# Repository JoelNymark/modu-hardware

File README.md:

# modu-hardware

KiCad hardware design files, schematics, PCB layouts, and 3D models for the **Modu** modular macro pad system. Modules connect magnetically via 4-pin pogo headers and communicate over a shared CAN bus.

> [!NOTE]
<!-- > Companion desktop control software: **[modu-app](https://github.com/RealWinter/modu-app)** -->

---

## Hardware Modules

| Hub Module (`hub-pcb`) | 4x4 Keypad Module (`4x4-key-pcb`) |
| :---: | :---: |
|  |  |
| Primary USB-C host controller and power/CAN bus bridge. | Snap-on 16-key mechanical switch matrix module. |

### 1. Hub PCB (`hub-pcb`)
The master controller module that interfaces with the host PC over USB-C and distributes power and CAN bus communication to connected satellite modules.
* **MCU:** STM32G0B1CBT6 (`U2`)
* **CAN Transceiver:** SN65HVD230DR (`U3`)
* **Power & Protection:** 3.3V regulation (`U1`), USB-C ESD protection (`U4`), and input reverse/surge protection (`D1`, `D2`)
* **Interconnects:** 6x perimeter 4-pin pogo pin header footprints (left, right, and bottom edges) for multi-directional module docking, plus SWD/debug headers (`J8`)

### 2. 4x4 Keypad PCB (`4x4-key-pcb`)
A 16-key modular keypad expansion board that can dock to the Hub or daisy-chain to other modules from any side.
* **MCU:** STM32G071CBT6 (`U2`)
* **CAN Transceiver:** SN65HVD230DR (`U3`)
* **Switch Matrix:** 4x4 mechanical key switch layout with individual per-key 1N4148W anti-ghosting diodes (`D1`–`D16`)
* **Interconnects:** 16x perimeter 4-pin pogo pin headers (4 per edge across all 4 sides) allowing flexible orientation and chaining

---

## Repository Structure

```text
modu-hardware/
├── hub-pcb/          # KiCad project, schematic, PCB, and STEP model for the Hub module
├── 4x4-key-pcb/      # KiCad project, schematic, PCB, and STEP model for the 4x4 Keypad module
├── hub-pcb.png       # 3D render of the Hub PCB
└── 4x4-key-pcb.png   # 3D render of the 4x4 Keypad PCB

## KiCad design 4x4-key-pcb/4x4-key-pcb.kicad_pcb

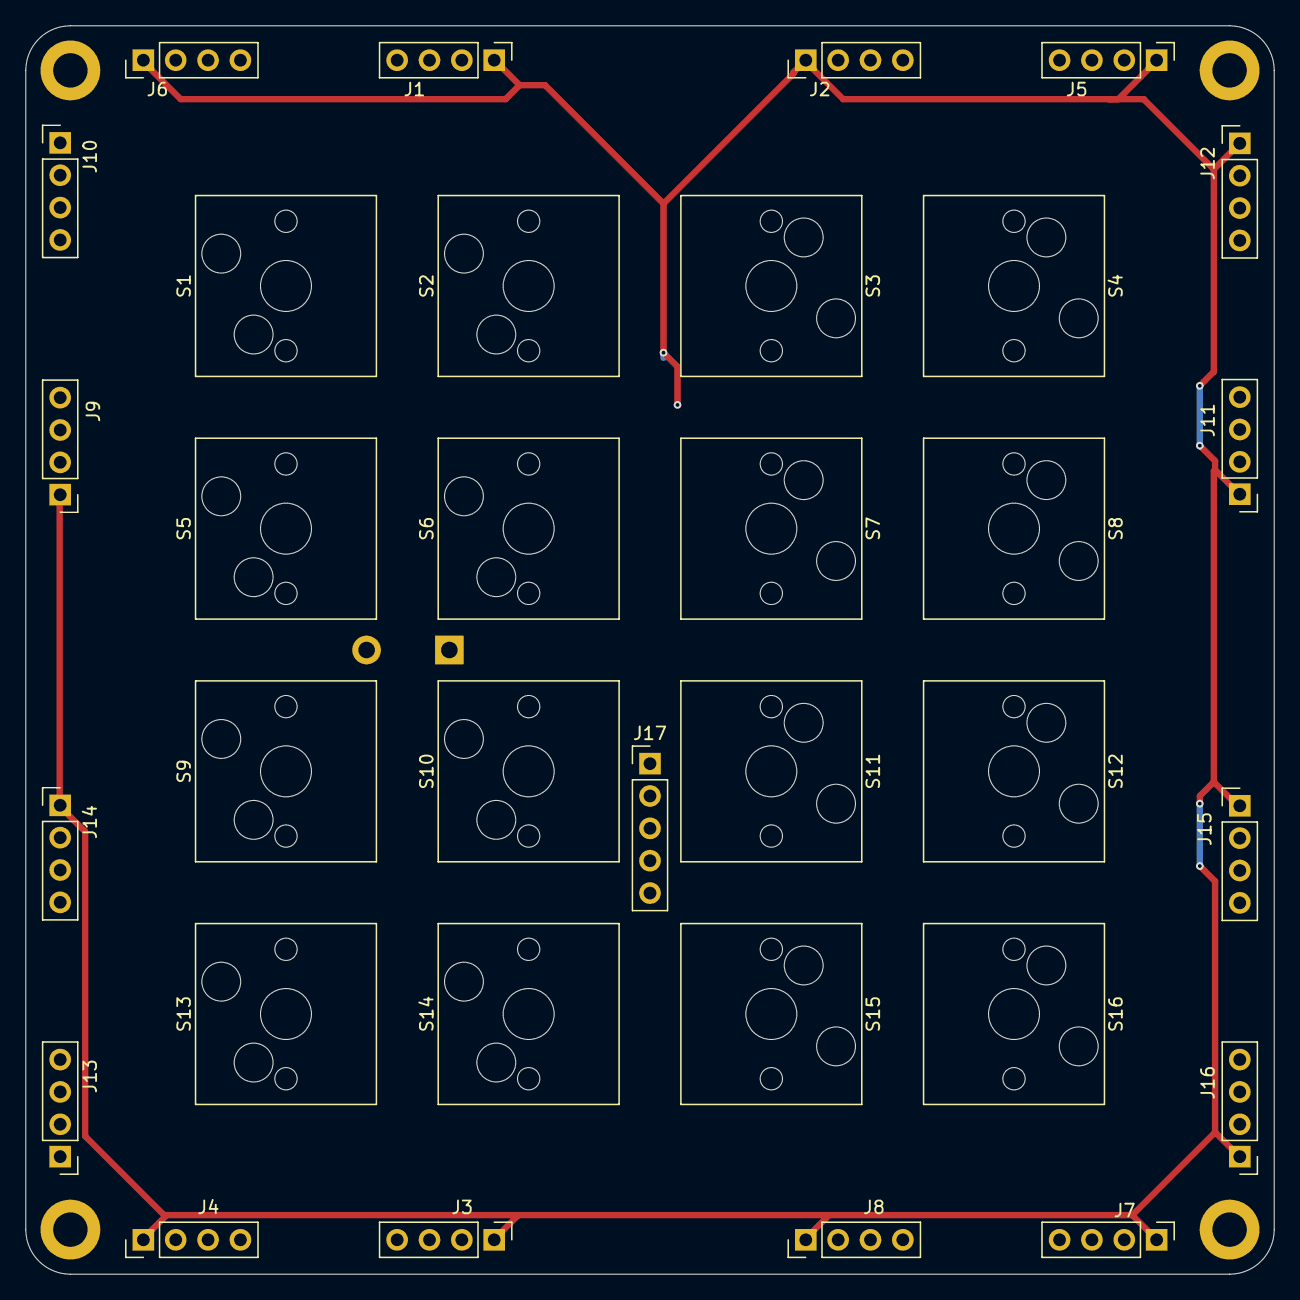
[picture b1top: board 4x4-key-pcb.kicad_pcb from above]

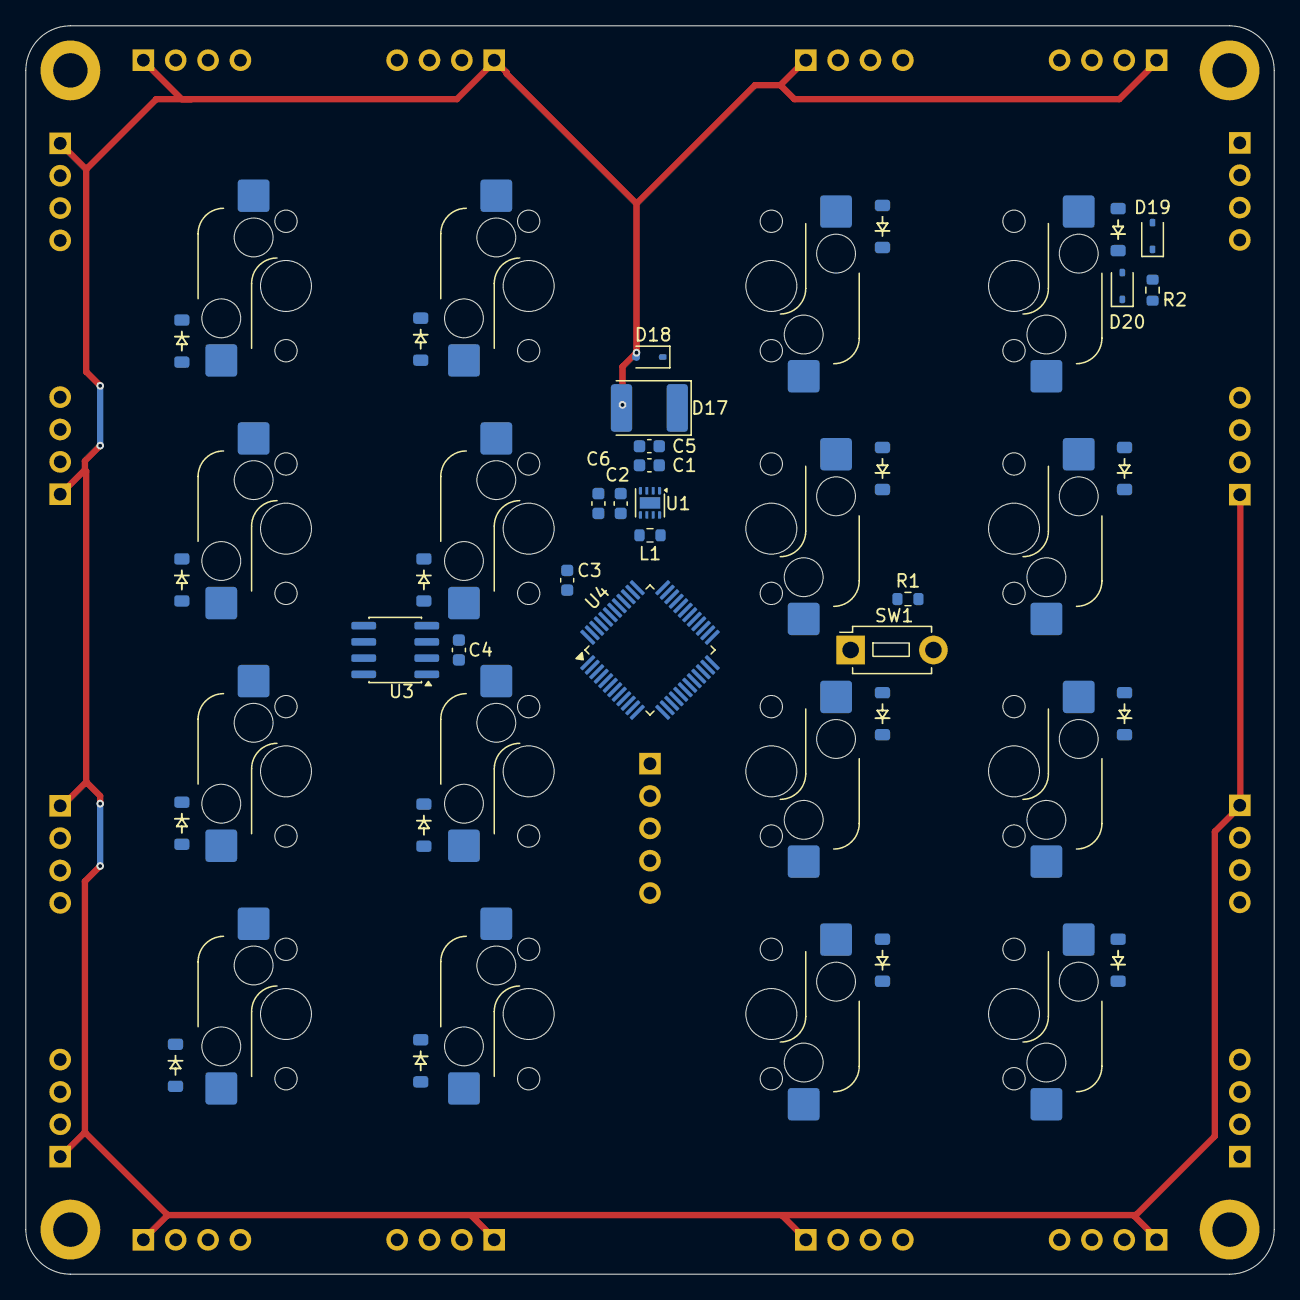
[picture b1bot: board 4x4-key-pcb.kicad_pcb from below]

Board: 2 copper layers, 98.0 x 98.0 mm, 66 parts (33 on the bottom side), 36 nets.

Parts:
C1: 10uF; C_0603_1608Metric
C2: 22uF; C_0603_1608Metric
C3, C4, C5, C6: 100nF; C_0603_1608Metric
D1, D2, D3, D4, D5, D6, D7, D8, D9, D10, D11, D12, D13, D14, D15, D16: Diode_SOD-123
D17: D_Schottky; D_2114_3652Metric
D18: 5.6V; D_SOD-323
D19, D20: D_TVS; D_SOD-323
J1, J2, J3, J4, J5, J6, J7, J8, J9, J10, J11, J12, J13, J14, J15, J16: Conn_01x04_Socket; PinHeader_1x04_P2.54mm_Vertical
J17: Conn_01x05_Pin; PinHeader_1x05_P2.54mm_Vertical
L1: 2.2uH; R_0603_1608Metric
R1: 10kΩ; R_0603_1608Metric
R2: R120Ω; R_0603_1608Metric
S1, S2, S3, S4, S5, S6, S7, S8, S9, S10, S11, S12, S13, S14, S15, S16: Hotswap_MX_1.00u
SW1: SW_Push; SW_PUSH_1P1T_6x3.5mm_H4.3_APEM_MJTP1243
U1: TPS62162DSG; Texas_DSG0008A_WSON-8-1EP_2x2mm_P0.5mm_EP0.9x1.6mm
U3: SN65HVD230; SOIC-8_3.9x4.9mm_P1.27mm
U4: STM32G0B1CBT6; LQFP-48_7x7mm_P0.5mm

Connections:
+3.3V: C2.1, C3.1, C4.1, C6.1, J17.1, L1.2, R1.1, U1.6 (VOS), U3.3 (VCC), U4.6 (VDD)
+5V: D17.2 (A), D18.2 (A2), J1.1, J2.1, J3.1, J4.1, J5.1, J6.1, J7.1, J8.1, J9.1, J10.1, J11.1, J12.1, J13.1, J14.1, J15.1, J16.1
C0: D1.1 (K), D2.1 (K), D3.1 (K), D4.1 (K), U4.21 (PB2)
C1: D5.1 (K), D6.1 (K), D7.1 (K), D8.1 (K), U4.42 (PB3)
C2: D9.1 (K), D10.1 (K), D11.1 (K), D12.1 (K), U4.45 (PB6)
C3: D13.1 (K), D14.1 (K), D15.1 (K), D16.1 (K), U4.46 (PB7)
CAN_H: D19.1 (A1), J1.3, J2.3, J3.3, J4.3, J5.3, J6.3, J7.3, J8.3, J9.3, J10.3, J11.3, J12.3, J13.3, J14.3, J15.3, J16.3, R2.1, U3.7 (CANH)
CAN_L: D20.1 (A1), J1.4, J2.4, J3.4, J4.4, J5.4, J6.4, J7.4, J8.4, J9.4, J10.4, J11.4, J12.4, J13.4, J14.4, J15.4, J16.4, R2.2, U3.6 (CANL)
CAN_RX: U3.4 (R), U4.33 (PA9/PA11)
CAN_TX: U3.1 (D), U4.32 (PA10/UCPD1_DBCC2)
GND: C1.2, C2.2, C3.2, C4.2, C5.1, C6.2, D18.1 (A1), D19.2 (A2), D20.2 (A2), J1.2, J2.2, J3.2, J4.2, J5.2, J6.2, J7.2, J8.2, J9.2, J10.2, J11.2, J12.2, J13.2, J14.2, J15.2, J16.2, J17.3, SW1.1, U1.1 (PGND), U1.4 (AGND), U1.5 (FB), U1.9 (PAD), U3.2 (GND), U3.8 (Rs), U4.7 (VSS)
unnamed: D1.2 (A), S1.2
unnamed: D2.2 (A), S2.2
unnamed: D3.2 (A), S3.2
unnamed: D4.2 (A), S4.2
unnamed: D5.2 (A), S5.2
unnamed: D6.2 (A), S6.2
unnamed: D7.2 (A), S7.2
unnamed: D8.2 (A), S8.2
unnamed: D9.2 (A), S9.2
unnamed: D10.2 (A), S10.2
unnamed: D11.2 (A), S11.2
unnamed: D12.2 (A), S12.2
unnamed: D13.2 (A), S13.2
unnamed: D14.2 (A), S14.2
unnamed: D15.2 (A), S15.2
unnamed: D16.2 (A), S16.2
unnamed: C1.1, C5.2, D17.1 (K), U1.2 (VIN), U1.3 (EN)
unnamed: L1.1, U1.7 (SW)
PF2: J17.5, R1.2, SW1.2, U4.10 (PF2)
R0: S1.1, S5.1, S9.1, S13.1, U4.19 (PB0)
R1: S2.1, S6.1, S10.1, S14.1, U4.20 (PB1)
R2: S3.1, S7.1, S11.1, S15.1, U4.43 (PB4)
R3: S4.1, S8.1, S12.1, S16.1, U4.44 (PB5)
SWCLK: J17.4, U4.36 (PA14)
SWDIO: J17.2, U4.35 (PA13)

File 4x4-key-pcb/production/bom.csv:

Designator,Footprint,Quantity,Value,LCSC Part #
C1,0603,1,10uF,
C2,0603,1,22uF,
"C3_2, C3, C4, C5, C6",0603,5,100nF,
"D1, D10, D11, D12, D13, D14, D15, D16, D2, D3, D4, D5, D6, D7, D8, D9",Diode_SOD-123,16,~,
D17,2114,1,D_Schottky,
"D18, D19, D20",D_SOD-323,3,D_TVS,
"J1, J10, J11, J12, J13, J14, J15, J16, J2, J3, J4, J5, J6, J7, J8, J9",PinHeader_1x04_P2.54mm_Vertical,16,Conn_01x04_Socket,
J17,PinHeader_1x05_P2.54mm_Vertical,1,Conn_01x05_Pin,
L1,0603,1,2.2uH,
R1,0603,1,10kΩ,
R2,0603,1,R120Ω,
"S1, S10, S11, S12, S13, S14, S15, S16, S2, S3, S4, S5, S6, S7, S8, S9",MX_PCB_1.00u,16,~,
SW1,SW_PUSH_1P1T_6x3.5mm_H4.3_APEM_MJTP1243,1,SW_Push,
U1,Texas_DSG0008A_WSON-8-1EP_2x2mm_P0.5mm_EP0.9x1.6mm,1,TPS62162DSG,
U3,SOIC-8_3.9x4.9mm_P1.27mm,1,SN65HVD230,
U4,LQFP-48_7x7mm_P0.5mm,1,STM32G0B1CBT6,

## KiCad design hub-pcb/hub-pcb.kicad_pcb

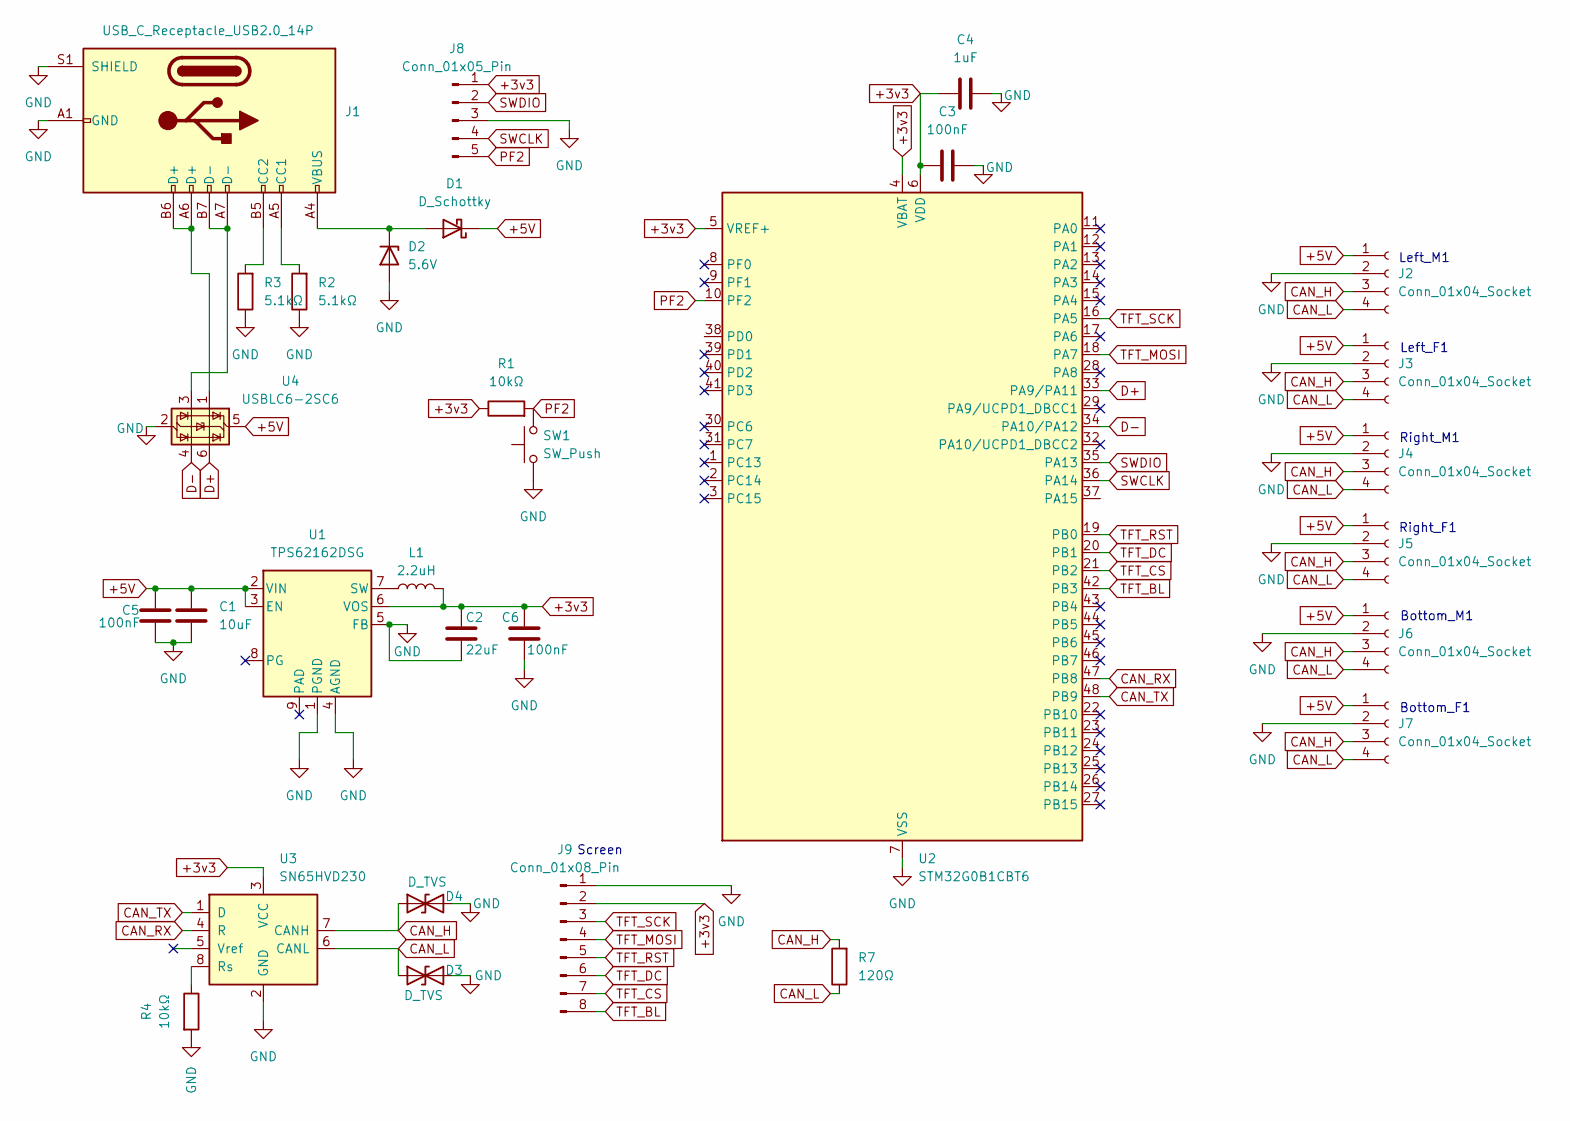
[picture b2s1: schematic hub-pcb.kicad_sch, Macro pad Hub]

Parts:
C1: 10uF; C_0603_1608Metric
C2: 22uF; C_0603_1608Metric
C3, C5, C6: 100nF; C_0603_1608Metric
C4: 1uF; C_0603_1608Metric
D1: D_Schottky; D_2114_3652Metric
D2: 5.6V; D_SOD-323
D3, D4: D_TVS; D_SOD-123
J1: USB_C_Receptacle_USB2.0_14P; USB_C_HRO_TYPE-C-31-M-12
J2, J3, J4, J5, J6, J7: Conn_01x04_Socket; PinHeader_1x04_P2.54mm_Vertical
J8: Conn_01x05_Pin; PinHeader_1x05_P2.54mm_Vertical
J9: Conn_01x08_Pin; PinHeader_1x08_P2.54mm_Vertical
L1: 2.2uH; R_0603_1608Metric
R1, R4: 10kΩ; R_0603_1608Metric
R2, R3: 5.1kΩ; R_0603_1608Metric
R7: 120Ω; R_0603_1608Metric
SW1: SW_Push; SW_PUSH_1P1T_6x3.5mm_H4.3_APEM_MJTP1243
U1: TPS62162DSG; Texas_DSG0008A_WSON-8-1EP_2x2mm_P0.5mm_EP0.9x1.6mm_ThermalV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
U2: STM32G0B1CBT6; LQFP-48_7x7mm_P0.5mm
U3: SN65HVD230; SOIC-8_3.9x4.9mm_P1.27mm
U4: USBLC6-2SC6; SOT-23-6

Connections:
+3v3: C2.1, C3.1, C4.1, C6.1, J8.1, J9.2, L1.2, R1.1, U1.6 (VOS), U2.4 (VBAT), U2.5 (VREF+), U2.6 (VDD), U3.3 (VCC)
+5V: C1.1, C5.1, D1.1 (K), J2.1, J3.1, J4.1, J5.1, J6.1, J7.1, U1.2 (VIN), U1.3 (EN), U4.5 (VBUS)
CAN_H: D4.1 (A1), J2.3, J3.3, J4.3, J5.3, J6.3, J7.3, R7.2, U3.7 (CANH)
CAN_L: D3.1 (A1), J2.4, J3.4, J4.4, J5.4, J6.4, J7.4, R7.1, U3.6 (CANL)
CAN_RX: U2.47 (PB8), U3.4 (R)
CAN_TX: U2.48 (PB9), U3.1 (D)
D+: U2.33 (PA9/PA11), U4.6 (I/O1)
D-: U2.34 (PA10/PA12), U4.4 (I/O2)
GND: C1.2, C2.2, C3.2, C4.2, C5.2, C6.2, D2.2 (A), D3.2 (A2), D4.2 (A2), J1.A1 (GND), J1.A12 (GND), J1.B1 (GND), J1.B12 (GND), J1.S1 (SHIELD), J2.2, J3.2, J4.2, J5.2, J6.2, J7.2, J8.3, J9.1, R2.1, R3.1, R4.2, SW1.1, U1.1 (PGND), U1.4 (AGND), U1.5 (FB), U2.7 (VSS), U3.2 (GND), U4.2 (GND)
unnamed: D1.2 (A), D2.1 (K), J1.A4 (VBUS), J1.A9 (VBUS), J1.B4 (VBUS), J1.B9 (VBUS)
unnamed: J1.A5 (CC1), R2.2
unnamed: J1.B5 (CC2), R3.2
unnamed: J1.A6 (D+), J1.B6 (D+), U4.1 (I/O1)
unnamed: J1.A7 (D-), J1.B7 (D-), U4.3 (I/O2)
unnamed: L1.1, U1.7 (SW)
unnamed: R4.1, U3.8 (Rs)
PF2: J8.5, R1.2, SW1.2, U2.10 (PF2)
SWCLK: J8.4, U2.36 (PA14)
SWDIO: J8.2, U2.35 (PA13)
TFT_BL: J9.8, U2.42 (PB3)
TFT_CS: J9.7, U2.21 (PB2)
TFT_DC: J9.6, U2.20 (PB1)
TFT_MOSI: J9.4, U2.18 (PA7)
TFT_RST: J9.5, U2.19 (PB0)
TFT_SCK: J9.3, U2.16 (PA5)

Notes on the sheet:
Right_M1
Right_F1
Left_M1
Left_F1
Bottom_F1
Screen
Bottom_M1

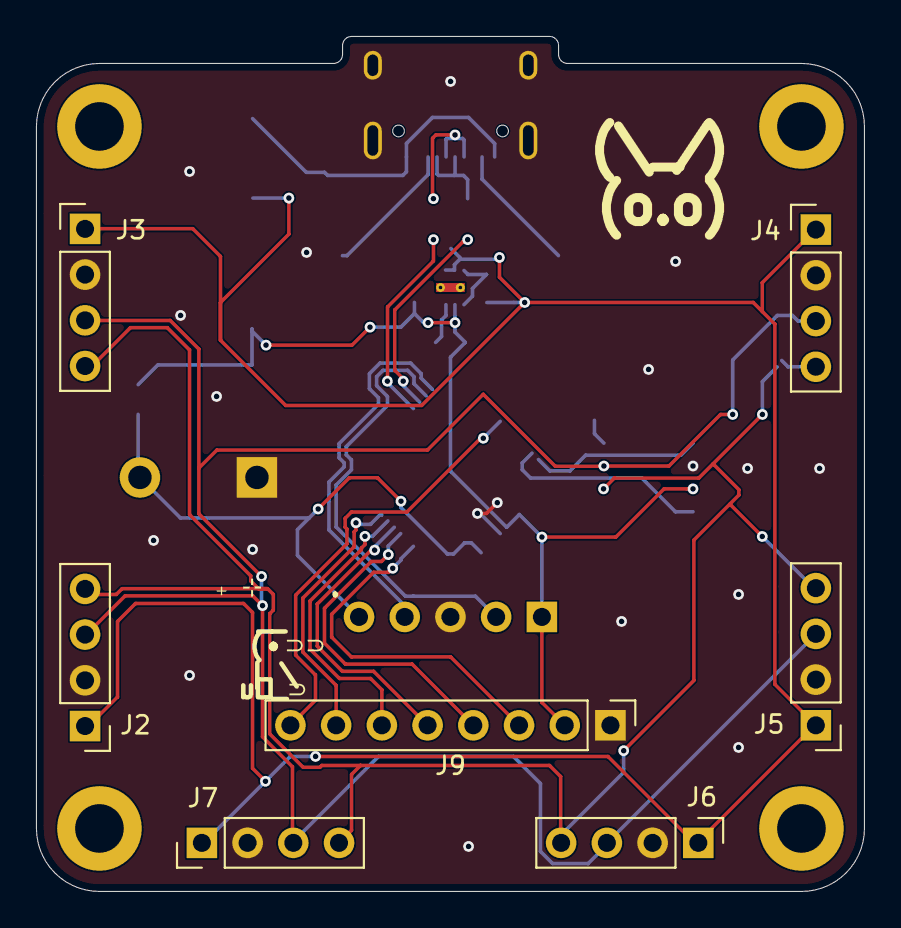
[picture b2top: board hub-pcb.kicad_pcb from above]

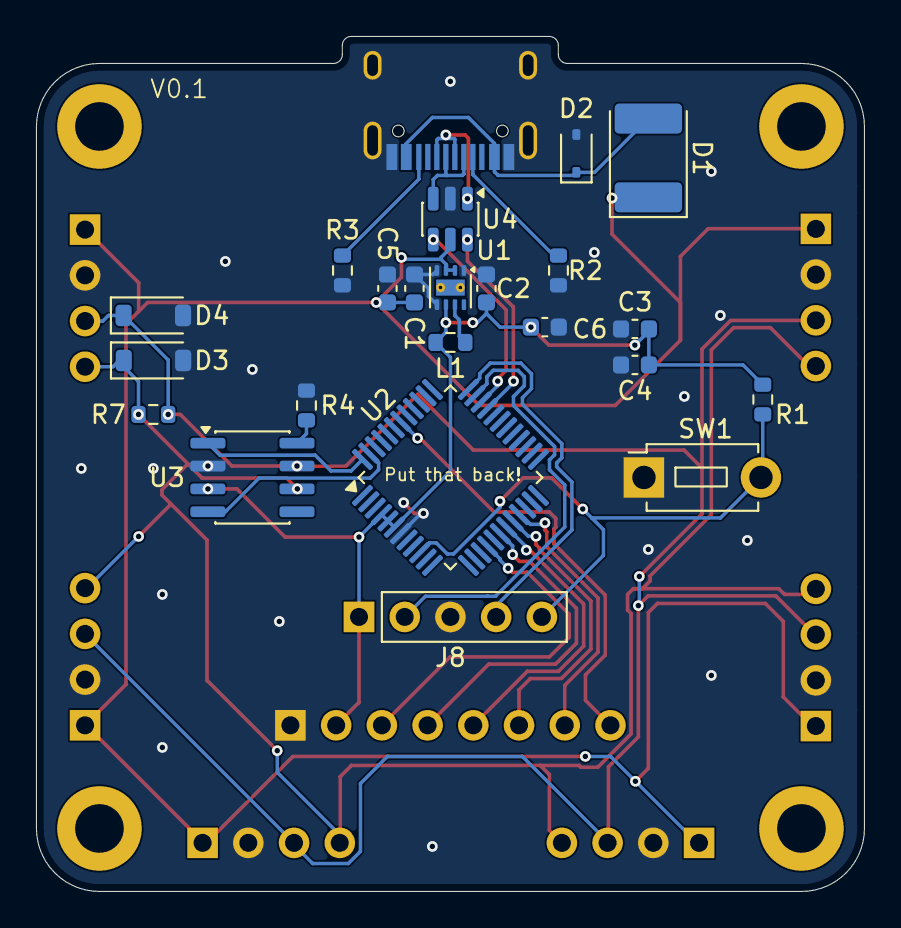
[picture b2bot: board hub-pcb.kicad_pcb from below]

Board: 2 copper layers, 46.0 x 47.5 mm, 30 parts (23 on the bottom side), 25 nets.

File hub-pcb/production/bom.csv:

Designator,Footprint,Quantity,Value,LCSC Part #
C1,0603,1,10uF,
C2,0603,1,22uF,
"C3, C5, C6",0603,3,100nF,
C4,0603,1,1uF,
D1,2114,1,D_Schottky,
D2,D_SOD-323,1,5.6V,
"D3, D4",D_SOD-123,2,D_TVS,
J1,USB_C_HRO_TYPE-C-31-M-12,1,USB_C_Receptacle_USB2.0_14P,
"J2, J3, J4, J5, J6, J7",PinHeader_1x04_P2.54mm_Vertical,6,Conn_01x04_Socket,
J8,PinHeader_1x05_P2.54mm_Vertical,1,Conn_01x05_Pin,
J9,PinHeader_1x08_P2.54mm_Vertical,1,Conn_01x08_Pin,
L1,0603,1,2.2uH,
"R1, R4",0603,2,10kΩ,
"R2, R3",0603,2,5.1kΩ,
R7,0603,1,120Ω,
SW1,SW_PUSH_1P1T_6x3.5mm_H4.3_APEM_MJTP1243,1,SW_Push,
U1,Texas_DSG0008A_WSON-8-1EP_2x2mm_P0.5mm_EP0.9x1.6mm_ThermalVias,1,TPS62162DSG,
U2,LQFP-48_7x7mm_P0.5mm,1,STM32G0B1CBT6,
U3,SOIC-8_3.9x4.9mm_P1.27mm,1,SN65HVD230,
U4,SOT-23-6,1,USBLC6-2SC6,

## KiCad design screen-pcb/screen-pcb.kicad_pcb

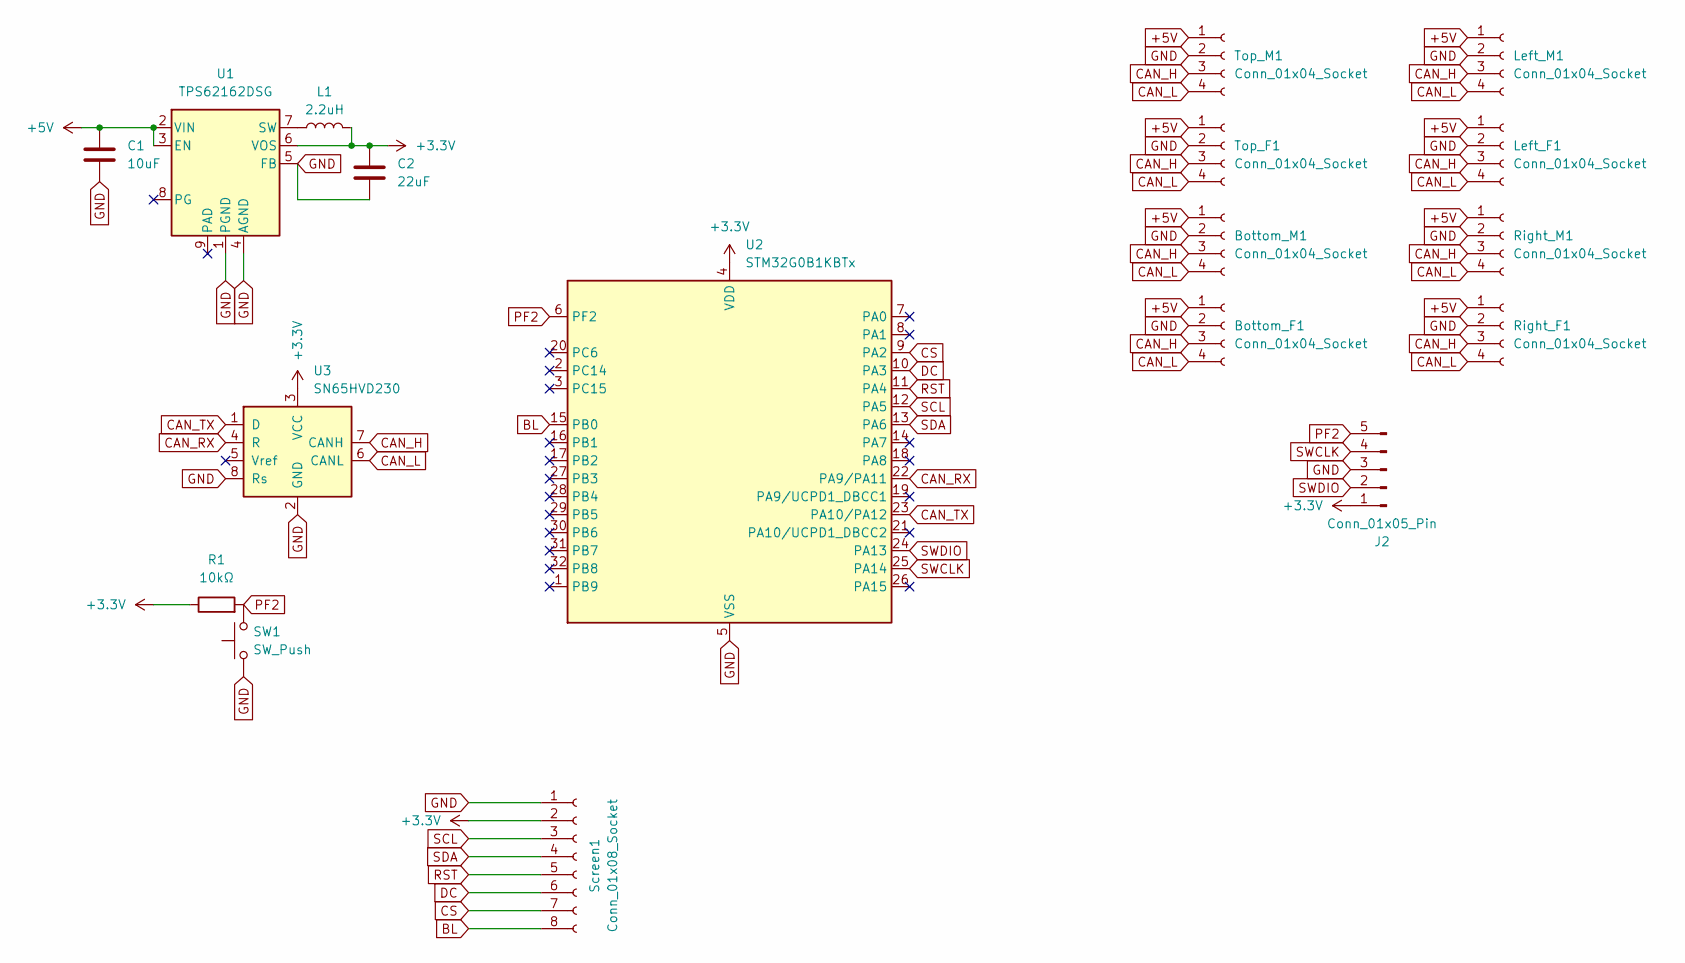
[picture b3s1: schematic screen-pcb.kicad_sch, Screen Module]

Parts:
Bottom_F1: Conn_01x04_Socket; PinHeader_1x04_P2.54mm_Vertical
Bottom_M1: Conn_01x04_Socket; PinHeader_1x04_P2.54mm_Vertical
C1: 10uF; C_0603_1608Metric
C2: 22uF; C_0603_1608Metric
J2: Conn_01x05_Pin; PinHeader_1x05_P2.54mm_Vertical
L1: 2.2uH; R_0603_1608Metric
Left_F1: Conn_01x04_Socket; PinHeader_1x04_P2.54mm_Vertical
Left_M1: Conn_01x04_Socket; PinHeader_1x04_P2.54mm_Vertical
R1: 10kΩ; R_0603_1608Metric
Right_F1: Conn_01x04_Socket; PinHeader_1x04_P2.54mm_Vertical
Right_M1: Conn_01x04_Socket; PinHeader_1x04_P2.54mm_Vertical
SW1: SW_Push; SW_SPST_FSMSM
Screen1: Conn_01x08_Socket; PinHeader_1x08_P2.54mm_Vertical
Top_F1: Conn_01x04_Socket; PinHeader_1x04_P2.54mm_Vertical
Top_M1: Conn_01x04_Socket; PinHeader_1x04_P2.54mm_Vertical
U1: TPS62162DSG; WSON-8-1EP_2x2mm_P0.5mm_EP0.9x1.6mm_ThermalVias
U2: STM32G0B1KBTx; LQFP-32_7x7mm_P0.8mm
U3: SN65HVD230; SOIC-8_3.9x4.9mm_P1.27mm

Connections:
+3.3V: C2.1, J2.1, L1.2, R1.1, Screen1.2, U1.6 (VOS), U2.4 (VDD), U3.3 (VCC)
+5V: Bottom_F1.1, Bottom_M1.1, C1.1, Left_F1.1, Left_M1.1, Right_F1.1, Right_M1.1, Top_F1.1, Top_M1.1, U1.2 (VIN), U1.3 (EN)
BL: Screen1.8, U2.15 (PB0)
CAN_H: Bottom_F1.3, Bottom_M1.3, Left_F1.3, Left_M1.3, Right_F1.3, Right_M1.3, Top_F1.3, Top_M1.3, U3.7 (CANH)
CAN_L: Bottom_F1.4, Bottom_M1.4, Left_F1.4, Left_M1.4, Right_F1.4, Right_M1.4, Top_F1.4, Top_M1.4, U3.6 (CANL)
CAN_RX: U2.22 (PA9/PA11), U3.4 (R)
CAN_TX: U2.23 (PA10/PA12), U3.1 (D)
CS: Screen1.7, U2.9 (PA2)
DC: Screen1.6, U2.10 (PA3)
GND: Bottom_F1.2, Bottom_M1.2, C1.2, C2.2, J2.3, Left_F1.2, Left_M1.2, Right_F1.2, Right_M1.2, SW1.1, Screen1.1, Top_F1.2, Top_M1.2, U1.1 (PGND), U1.4 (AGND), U1.5 (FB), U2.5 (VSS), U3.2 (GND), U3.8 (Rs)
unnamed: L1.1, U1.7 (SW)
PF2: J2.5, R1.2, SW1.2, U2.6 (PF2)
RST: Screen1.5, U2.11 (PA4)
SCL: Screen1.3, U2.12 (PA5)
SDA: Screen1.4, U2.13 (PA6)
SWCLK: J2.4, U2.25 (PA14)
SWDIO: J2.2, U2.24 (PA13)

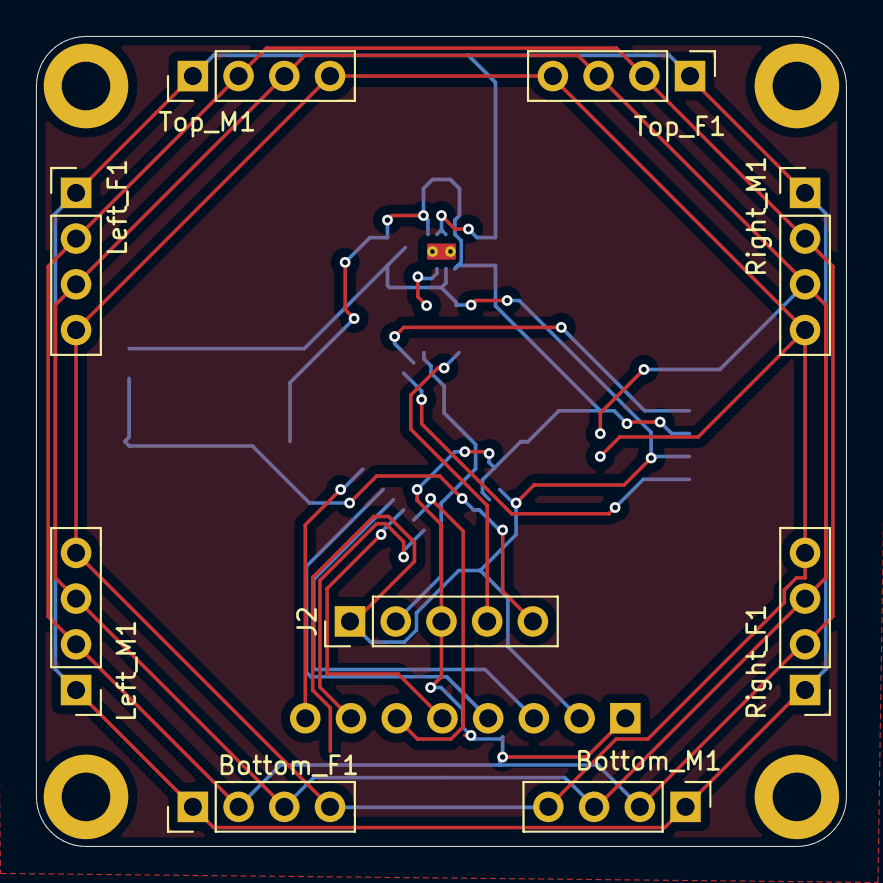
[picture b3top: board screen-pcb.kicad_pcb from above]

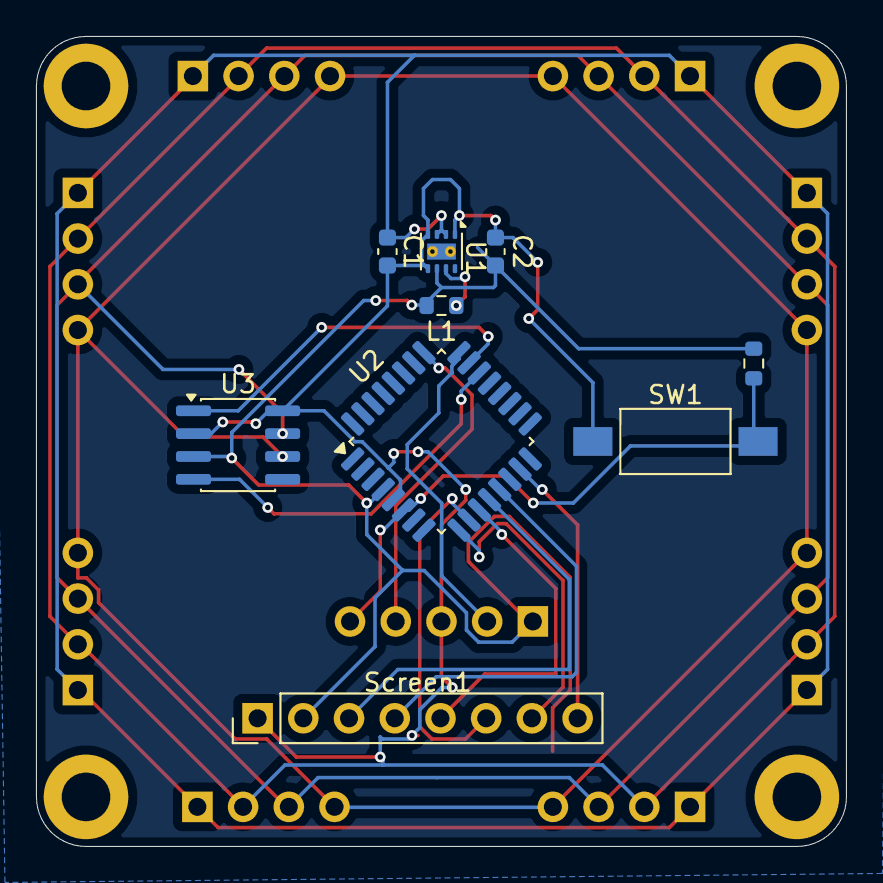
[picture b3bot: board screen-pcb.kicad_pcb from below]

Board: 2 copper layers, 45.0 x 45.0 mm, 18 parts (9 on the bottom side), 17 nets.

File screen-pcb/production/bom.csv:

Designator,Footprint,Quantity,Value,LCSC Part #
"BOTTOM_F1, BOTTOM_M1, LEFT_F1, LEFT_M1, RIGHT_F1, RIGHT_M1, TOP_F1, TOP_M1",PinHeader_1x04_P2.54mm_Vertical,8,Conn_01x04_Socket,
C1,0603,1,10uF,
C2,0603,1,22uF,
J2,PinHeader_1x05_P2.54mm_Vertical,1,Conn_01x05_Pin,
L1,0603,1,2.2uH,
R1,0603,1,10kΩ,
SCREEN1,PinHeader_1x08_P2.54mm_Vertical,1,Conn_01x08_Socket,
SW1,SW_SPST_FSMSM,1,SW_Push,
U1,WSON-8-1EP_2x2mm_P0.5mm_EP0.9x1.6mm_ThermalVias,1,TPS62162DSG,
U2,LQFP-32_7x7mm_P0.8mm,1,STM32G0B1KBTx,
U3,SOIC-8_3.9x4.9mm_P1.27mm,1,SN65HVD230,
